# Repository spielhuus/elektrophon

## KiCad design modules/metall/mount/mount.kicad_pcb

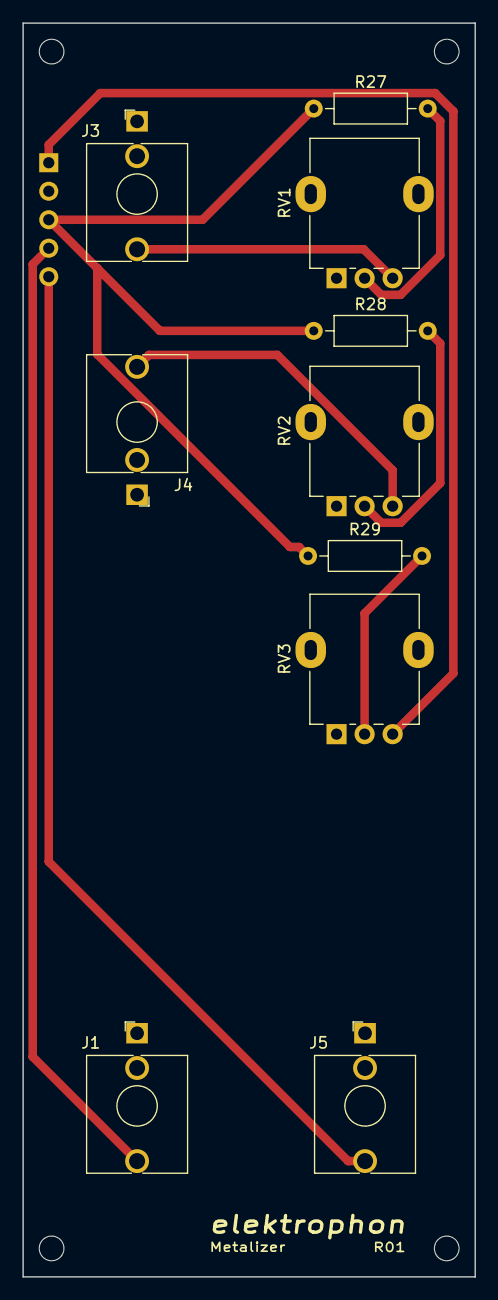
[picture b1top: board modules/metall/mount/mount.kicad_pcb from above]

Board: 2 copper layers, 40.3 x 111.8 mm, 15 parts (1 on the bottom side), 10 nets.

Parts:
H1, H2, H3, H4: MountingHole; MountingHole_2.2mm_M2
J1: INPUT; Jack_3.5mm_WQP-PJ398SM_Vertical
J2: Conn_01x05_Male; PinHeader_1x05_P2.54mm_Vertical
J3: CV1; Jack_3.5mm_WQP-PJ398SM_Vertical
J4: CV2; Jack_3.5mm_WQP-PJ398SM_Vertical
J5: OUT; Jack_3.5mm_WQP-PJ398SM_Vertical
R27, R28, R29: 270k; R_Axial_DIN0207_L6.3mm_D2.5mm_P10.16mm_Horizontal
RV1, RV2, RV3: 100k; Potentiometer_Alpha_RD901F-40-00D_Single_Vertical

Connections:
+15V: J2.1, RV3.3
/CV: J2.3, R27.1, R28.1, R29.1
/IN: J1.T, J2.4
/OUT: J2.5, J5.T
GND: J1.S, J2.2, J3.S, J4.S, J5.S, RV1.1, RV2.1, RV3.1
unnamed: J3.T, RV1.3
unnamed: J4.T, RV2.3
unnamed: R27.2, RV1.2
unnamed: R28.2, RV2.2
unnamed: R29.2, RV3.2

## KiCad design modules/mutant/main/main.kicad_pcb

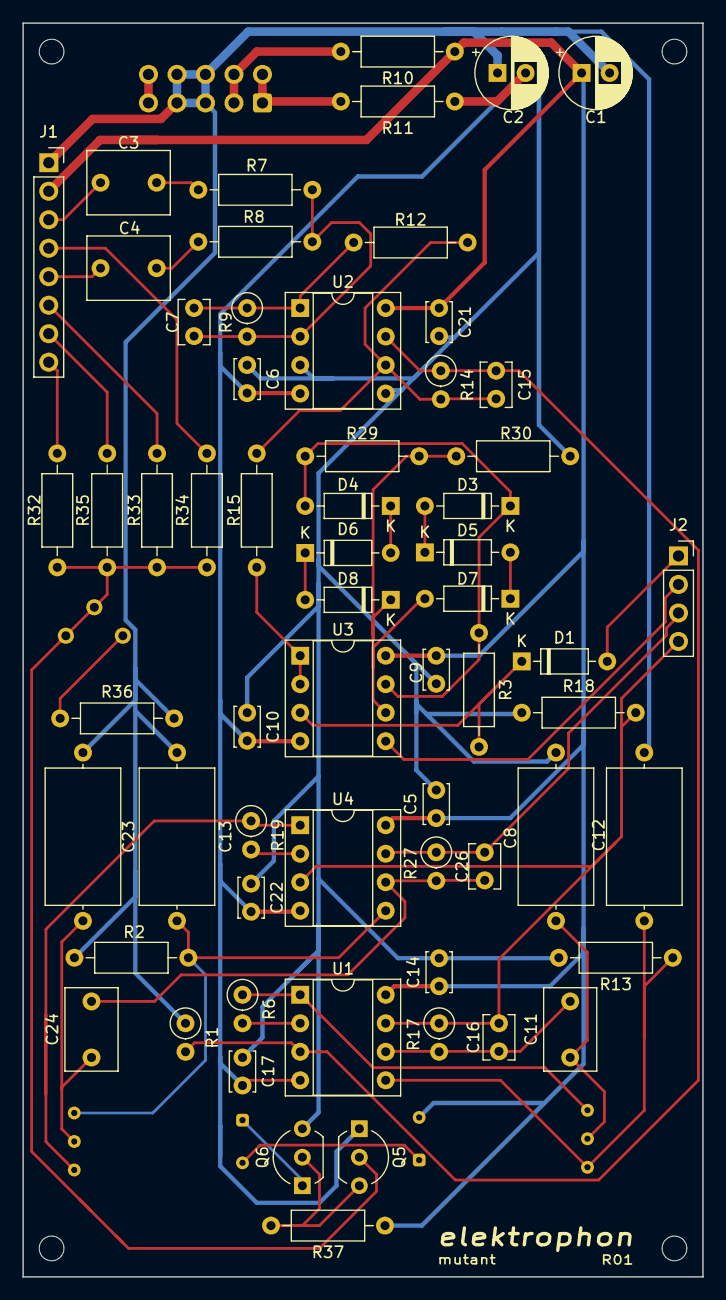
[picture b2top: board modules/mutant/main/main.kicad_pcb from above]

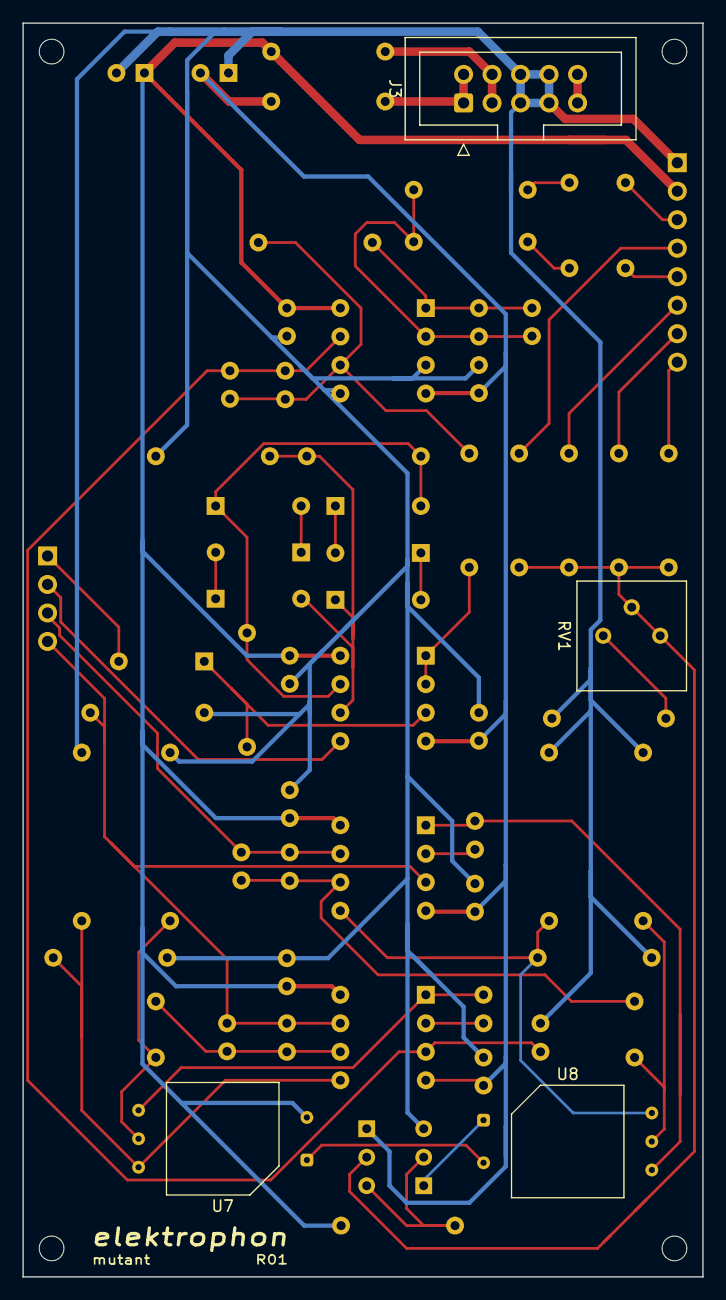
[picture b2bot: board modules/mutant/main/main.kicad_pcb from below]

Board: 2 copper layers, 60.6 x 111.8 mm, 70 parts (4 on the bottom side), 45 nets.

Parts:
C1, C2: 22u; CP_Radial_D6.3mm_P2.50mm
C3, C4: 1u (NP); C_Rect_L7.2mm_W5.5mm_P5.00mm_FKS2_FKP2_MKS2_MKP2
C5, C6, C9, C10, C14, C17, C21, C22: 0.1u; C_Disc_D3.4mm_W2.1mm_P2.50mm
C7, C15, C16, C26: 47p; C_Disc_D3.8mm_W2.6mm_P2.50mm
C8, C23: 220p; C_Axial_L12.0mm_D6.5mm_P15.00mm_Horizontal
C11, C24: 4700p; C_Rect_L7.2mm_W4.5mm_P5.00mm_FKS2_FKP2_MKS2_MKP2
C12, C13: 1000p; C_Axial_L12.0mm_D6.5mm_P15.00mm_Horizontal
D1, D3, D4, D5, D6, D7, D8: 1N4148; D_DO-35_SOD27_P7.62mm_Horizontal
J1: Conn_01x08_Female; PinSocket_1x08_P2.54mm_Vertical
J2: Conn_01x04_Female; PinSocket_1x04_P2.54mm_Vertical
J3: IDC Header; IDC-Header_2x05_P2.54mm_Vertical
Q5: BC557; TO-92_Inline_Wide
Q6: BC547; TO-92_Inline_Wide
R1, R9, R14: 100k; R_Axial_DIN0207_L6.3mm_D2.5mm_P2.54mm_Vertical
R2, R13: 4.7M; R_Axial_DIN0207_L6.3mm_D2.5mm_P10.16mm_Horizontal
R3, R7, R8, R12, R15, R18: 100k; R_Axial_DIN0207_L6.3mm_D2.5mm_P10.16mm_Horizontal
R6, R19: 15k; R_Axial_DIN0207_L6.3mm_D2.5mm_P2.54mm_Vertical
R10, R11: 10; R_Axial_DIN0207_L6.3mm_D2.5mm_P10.16mm_Horizontal
R17, R27: 10k; R_Axial_DIN0207_L6.3mm_D2.5mm_P2.54mm_Vertical
R29: 10k; R_Axial_DIN0207_L6.3mm_D2.5mm_P10.16mm_Horizontal
R30: 1.8k; R_Axial_DIN0207_L6.3mm_D2.5mm_P10.16mm_Horizontal
R32, R33, R34, R35: 110k; R_Axial_DIN0207_L6.3mm_D2.5mm_P10.16mm_Horizontal
R36: 1.5k; R_Axial_DIN0207_L6.3mm_D2.5mm_P10.16mm_Horizontal
R37: 1Meg; R_Axial_DIN0207_L6.3mm_D2.5mm_P10.16mm_Horizontal
REF1, REF2, REF3, REF4: MountingHole_2.2mm_M2
RV1: 1k; Potentiometer_Bourns_3386P_Vertical
U1, U2, U3, U4: TL072; DIP-8_W7.62mm_Socket
U7, U8: VTL5Cx2; PerkinElmer_VTL5Cx2

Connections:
+5V: J3.9, J3.10
+15V: C1.1, C5.1, C9.1, C14.1, C21.1, J1.2, R10.1, R37.1, U1.8, U2.8, U3.8, U4.8, U7.2
-15V: C2.2, C6.2, C10.2, C17.2, C22.2, Q5.1, R11.1, U1.4, U2.4, U3.4, U4.4
/V1a: R6.1, U1.1, U7.5
/V1b: C8.2, C11.1, U7.4
/V1c: C12.2, R13.1, U1.5, U7.3
/V2a: R19.1, U4.1, U8.5
/V2b: C23.2, C24.1, U8.4
/V2c: C13.2, R2.1, U4.5, U8.3
CLIP: D1.2, J2.1
CV: J1.7, R35.2
CV2: J1.8, R32.2
FREQ: J1.4, R34.2
GND: C1.2, C2.1, C5.2, C6.1, C8.1, C9.2, C10.1, C12.1, C13.1, C14.2, C17.1, C21.2, C22.1, C23.1, J1.1, J3.5, J3.6, J3.7, J3.8, Q6.3, R1.1, R2.2, R13.2, R18.1, R30.1, R36.2, U2.3, U2.5
IN_1: C3.2, J1.3
IN_2: C4.2, J1.5
unnamed: C3.1, R7.2
unnamed: C4.1, R8.2
unnamed: C7.1, R9.1, R12.2, U2.1
unnamed: C7.2, R7.1, R8.1, R9.2, U2.2
unnamed: C11.2, C16.2, R17.2, U1.6
unnamed: C15.1, R1.2, R14.1, U1.3, U2.7
unnamed: C15.2, R12.1, R14.2, R15.2, U2.6
unnamed: C24.2, C26.2, R27.2, U4.6
unnamed: D1.1, R3.2, U3.3
unnamed: D3.1, D4.2, R3.1, R29.2, U3.7
unnamed: D3.2, D5.1
unnamed: D4.1, D6.2
unnamed: D5.2, D7.1
unnamed: D6.1, D8.2
unnamed: D7.2, D8.1, R29.1, R30.2, U3.6
unnamed: Q5.2, R32.1, R33.1, R34.1, R35.1, RV1.1, RV1.2
unnamed: Q5.3, Q6.2, R37.2
unnamed: Q6.1, U8.1
unnamed: R6.2, U1.2
unnamed: R15.1, U3.1, U3.2
unnamed: R19.2, U4.2
unnamed: R36.1, RV1.3
unnamed: U7.1, U8.2
OUT_A: C16.1, J2.4, R17.1, R18.2, U1.7, U4.3
OUT_B: C26.1, J2.3, R27.1, U4.7
RES: J2.2, U3.5
VN: J3.1, J3.2, R11.2
VP: J3.3, J3.4, R10.2
V_OCT: J1.6, R33.2

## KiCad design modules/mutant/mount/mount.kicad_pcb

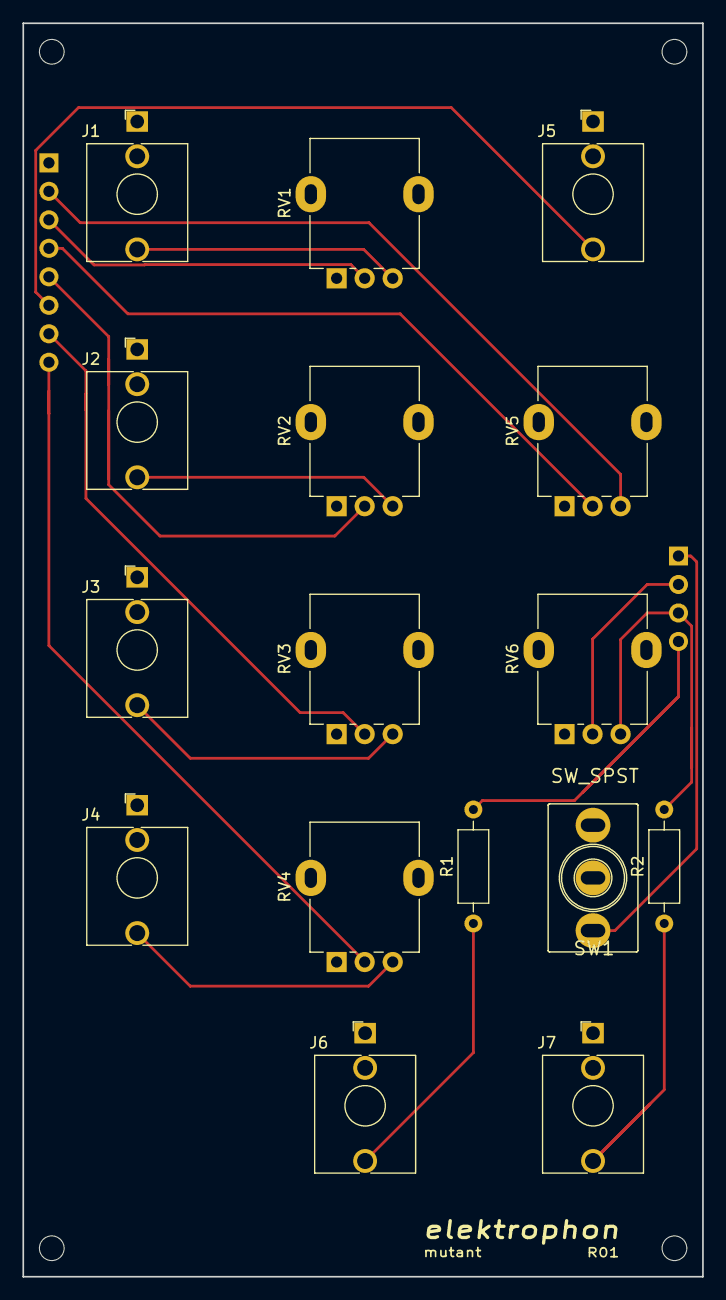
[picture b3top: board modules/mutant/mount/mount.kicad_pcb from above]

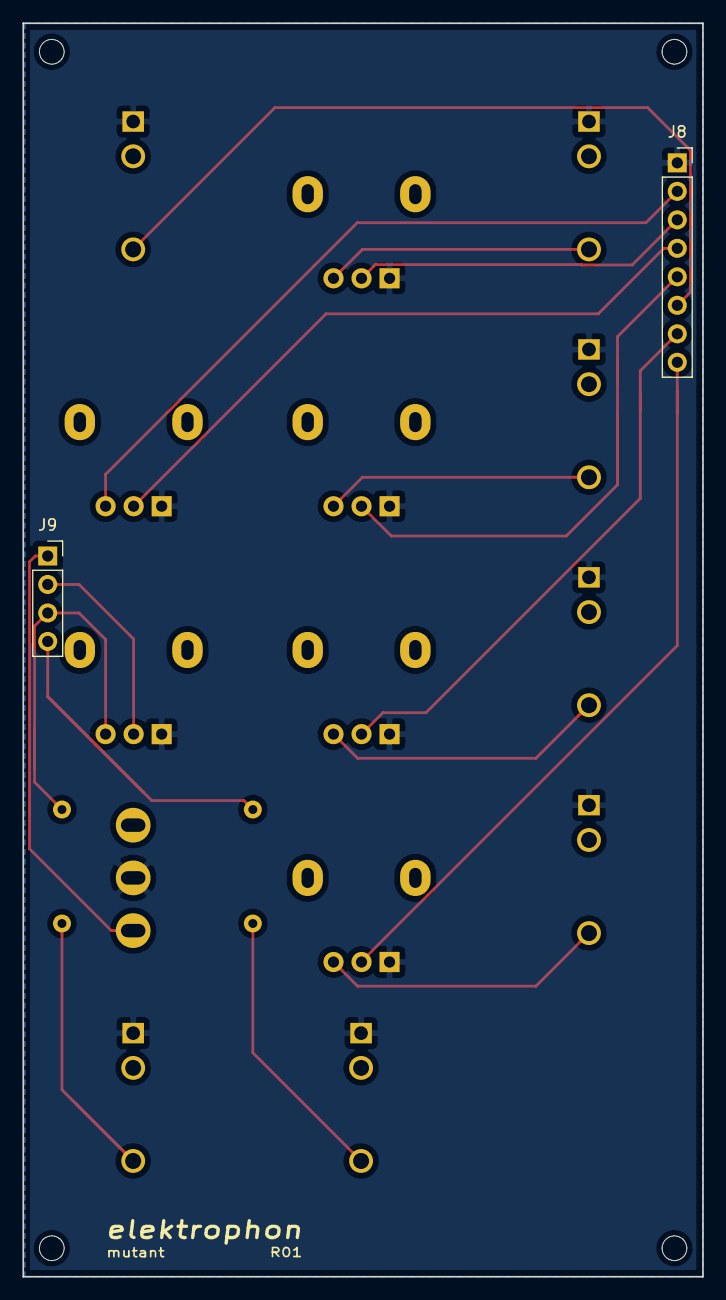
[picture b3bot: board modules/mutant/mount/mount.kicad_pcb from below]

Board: 2 copper layers, 60.6 x 111.8 mm, 22 parts (2 on the bottom side), 18 nets.

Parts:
J1: IN1; Jack_3.5mm_WQP-PJ398SM_Vertical
J2: IN2; Jack_3.5mm_WQP-PJ398SM_Vertical
J3: CV1; Jack_3.5mm_WQP-PJ398SM_Vertical
J4: CV2; Jack_3.5mm_WQP-PJ398SM_Vertical
J5: V/OCT; Jack_3.5mm_WQP-PJ398SM_Vertical
J6: OUt_1; Jack_3.5mm_WQP-PJ398SM_Vertical
J7: OUT_2; Jack_3.5mm_WQP-PJ398SM_Vertical
J8: Conn_01x08_Male; PinSocket_1x08_P2.54mm_Vertical
J9: Conn_01x04_Male; PinSocket_1x04_P2.54mm_Vertical
R1, R2: 1k; R_Axial_DIN0207_L6.3mm_D2.5mm_P10.16mm_Horizontal
REF1, REF2, REF3, REF4: MountingHole_2.2mm_M2
RV1, RV2: 100k; Potentiometer_Alpha_RD901F-40-00D_Single_Vertical
RV3, RV4: 50k; Potentiometer_Alpha_RD901F-40-00D_Single_Vertical
RV5: 20k; Potentiometer_Alpha_RD901F-40-00D_Single_Vertical
RV6: 50k (log); Potentiometer_Alpha_RD901F-40-00D_Single_Vertical
SW1: SW_SPST; SPDT_KIT

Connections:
+15V: J8.2, RV5.3
CLIP: J9.1, SW1.1
CV: J8.7, RV3.2
CV2: J8.8, RV4.2
FREQ: J8.4, RV5.2
GND: J1.S, J2.S, J3.S, J4.S, J5.S, J6.S, J7.S, J8.1, RV1.1, RV2.1, RV3.1, RV4.1, RV5.1, RV6.1, SW1.2
IN_1: J8.3, RV1.2
IN_2: J8.5, RV2.2
unnamed: J1.T, RV1.3
unnamed: J2.T, RV2.3
unnamed: J3.T, RV3.3
unnamed: J4.T, RV4.3
unnamed: J6.T, R1.1
unnamed: J7.T, R2.1
OUT_A: J9.4, R1.2
OUT_B: J9.3, R2.2, RV6.3
RES: J9.2, RV6.2
V_OCT: J5.T, J8.6

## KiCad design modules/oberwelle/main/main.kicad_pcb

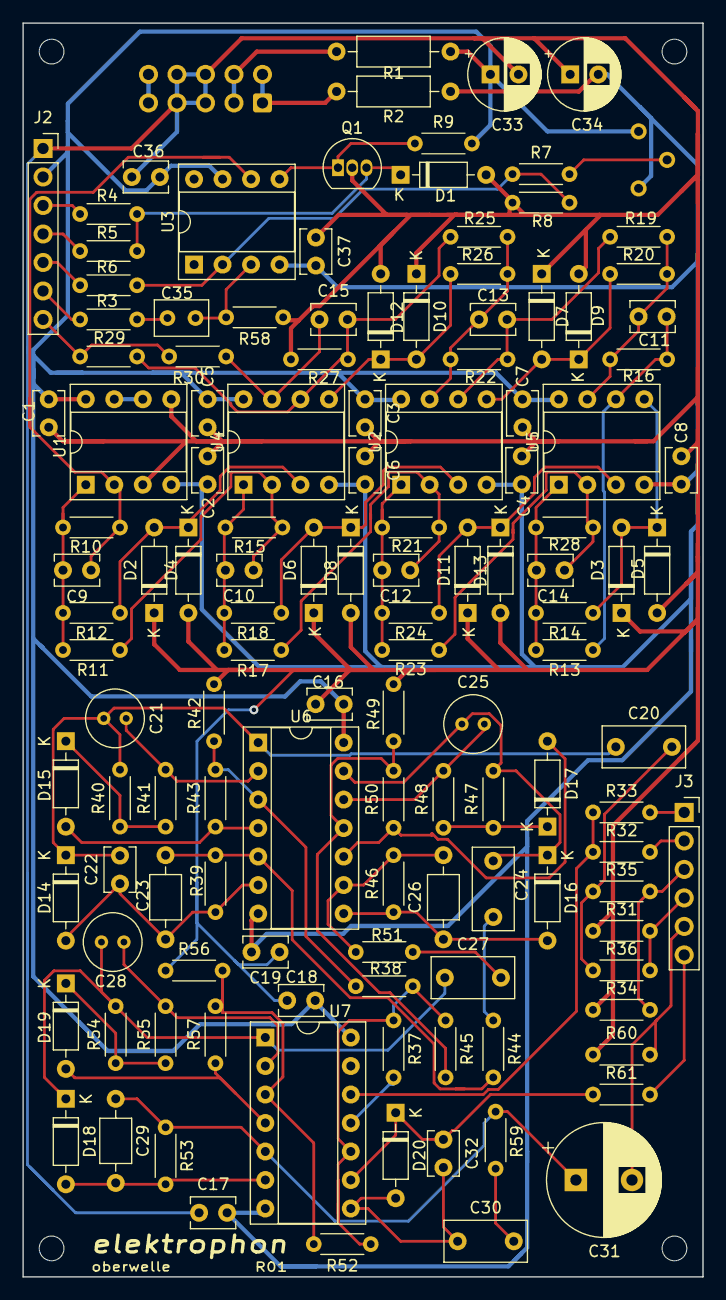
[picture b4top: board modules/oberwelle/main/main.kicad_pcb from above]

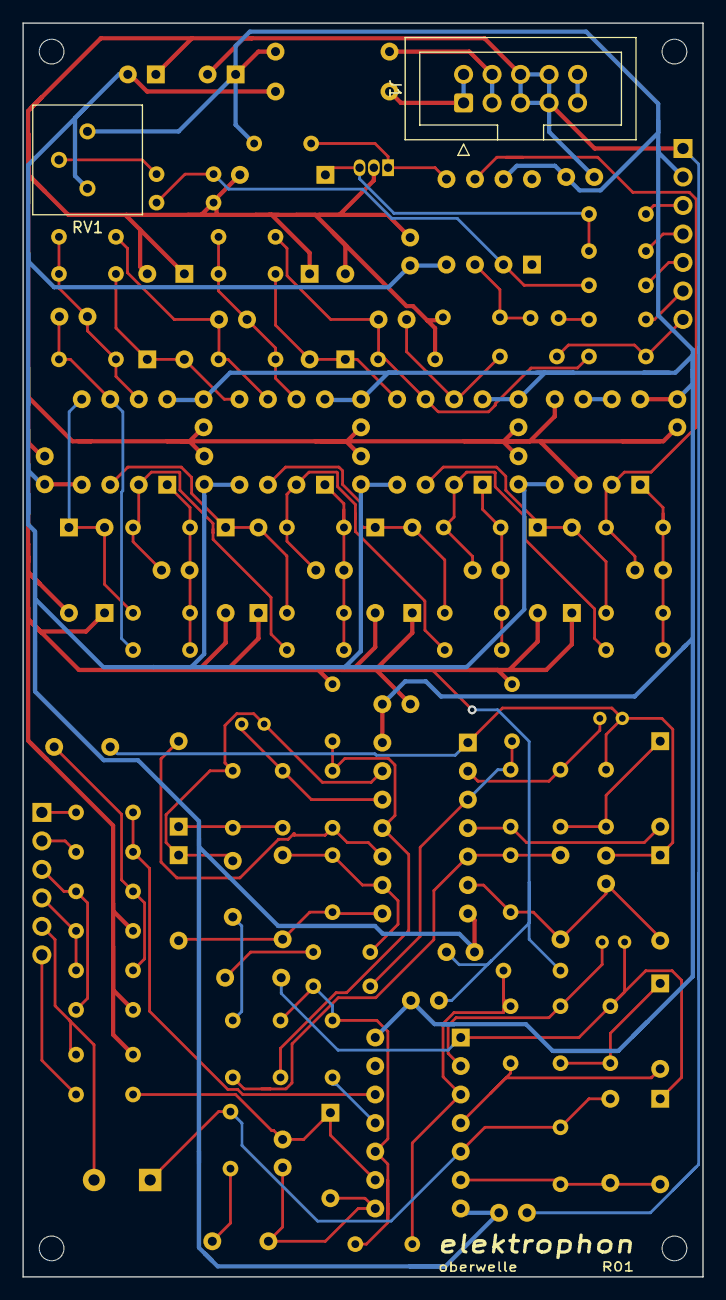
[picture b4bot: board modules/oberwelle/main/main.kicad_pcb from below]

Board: 2 copper layers, 60.6 x 111.8 mm, 134 parts (2 on the bottom side), 74 nets.

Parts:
C1, C2, C3, C4, C5, C6, C7, C8, C16, C17, C18, C19, C36, C37: 0.1u; C_Disc_D3.8mm_W2.6mm_P2.50mm
C9: 150p; C_Disc_D3.8mm_W2.6mm_P2.50mm
C10, C11, C12, C13, C14, C15, C22: 47p; C_Disc_D3.8mm_W2.6mm_P2.50mm
C20, C24, C27, C30: 47n; C_Rect_L7.2mm_W3.5mm_P5.00mm_FKS2_FKP2_MKS2_MKP2
C21: 1u (BP); C_Radial_D5.0mm_H7.0mm_P2.00mm
C23, C26, C29: 30p; C_Axial_L3.8mm_D2.6mm_P7.50mm_Horizontal
C25, C28: 1u (BP); C_Radial_D5.0mm_H5.0mm_P2.00mm
C31: 47u; CP_Radial_D10.0mm_P5.00mm
C32: 30p; C_Disc_D3.8mm_W2.6mm_P2.50mm
C33, C34: 22u; CP_Radial_D6.3mm_P2.50mm
C35: 220n; C_Rect_L4.6mm_W3.0mm_P2.50mm_MKS02_FKP02
D1, D2, D3, D4, D5, D6, D7, D8, D9, D10, D11, D12, D13, D14, D15, D16, D17, D18, D19: 1N4148; D_DO-35_SOD27_P7.62mm_Horizontal
D20: 4.3V/400mW; D_DO-35_SOD27_P7.62mm_Horizontal
J1: IDC Header; IDC-Header_2x05_P2.54mm_Vertical
J2: Conn_01x07_Female; PinSocket_1x07_P2.54mm_Vertical
J3: Conn_01x06_Female; PinSocket_1x06_P2.54mm_Vertical
Q1: BC557; TO-92_Inline
R1, R2: 10; R_Axial_DIN0207_L6.3mm_D2.5mm_P10.16mm_Horizontal
R3, R6, R11, R13, R15, R16, R17, R19, R21, R22, R23, R25, R28, R29, R31, R33, R34, R59, R60: 100k; R_Axial_DIN0204_L3.6mm_D1.6mm_P5.08mm_Horizontal
R4: 47k; R_Axial_DIN0204_L3.6mm_D1.6mm_P5.08mm_Horizontal
R5: 15k; R_Axial_DIN0204_L3.6mm_D1.6mm_P5.08mm_Horizontal
R7: 3.3meg; R_Axial_DIN0204_L3.6mm_D1.6mm_P5.08mm_Horizontal
R8, R58: 1.5k; R_Axial_DIN0204_L3.6mm_D1.6mm_P5.08mm_Horizontal
R9: 6.8meg; R_Axial_DIN0204_L3.6mm_D1.6mm_P5.08mm_Horizontal
R10: 82k; R_Axial_DIN0204_L3.6mm_D1.6mm_P5.08mm_Horizontal
R12, R14, R18, R20, R24, R26: 33k; R_Axial_DIN0204_L3.6mm_D1.6mm_P5.08mm_Horizontal
R27: 10k; R_Axial_DIN0204_L3.6mm_D1.6mm_P5.08mm_Horizontal
R30: 330; R_Axial_DIN0204_L3.6mm_D1.6mm_P5.08mm_Horizontal
R32, R38: 220k; R_Axial_DIN0204_L3.6mm_D1.6mm_P5.08mm_Horizontal
R35, R36, R43, R44, R51: 1meg; R_Axial_DIN0204_L3.6mm_D1.6mm_P5.08mm_Horizontal
R37: 150k; R_Axial_DIN0204_L3.6mm_D1.6mm_P5.08mm_Horizontal
R39, R46, R53, R57: 2.2meg; R_Axial_DIN0204_L3.6mm_D1.6mm_P5.08mm_Horizontal
R40, R41, R47, R48, R54, R55: 10meg; R_Axial_DIN0204_L3.6mm_D1.6mm_P5.08mm_Horizontal
R42, R49, R56: 820k; R_Axial_DIN0204_L3.6mm_D1.6mm_P5.08mm_Horizontal
R45: 330k; R_Axial_DIN0204_L3.6mm_D1.6mm_P5.08mm_Horizontal
R50: 1.5meg; R_Axial_DIN0204_L3.6mm_D1.6mm_P5.08mm_Horizontal
R52: 470k; R_Axial_DIN0204_L3.6mm_D1.6mm_P5.08mm_Horizontal
R61: 3.3k; R_Axial_DIN0204_L3.6mm_D1.6mm_P5.08mm_Horizontal
REF1, REF2, REF3, REF4: MountingHole_2.2mm_M2
RV1: 100k; Potentiometer_Bourns_3386P_Vertical
U1, U2, U4, U5: TL072; DIP-8_W7.62mm_Socket
U3: CA3080; DIP-8_W7.62mm_Socket
U6, U7: LM3900; DIP-14_W7.62mm_Socket

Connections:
+5V: J1.9, J1.10
+15V: C1.1, C3.1, C5.1, C7.1, C16.1, C18.1, C33.1, C36.1, J2.2, R1.1, R9.2, RV1.1, U1.8, U2.8, U3.7, U4.8, U5.8, U6.14, U7.14
-15V: C2.2, C4.2, C6.2, C8.2, C17.2, C19.2, C34.2, C37.2, R2.1, RV1.3, U1.4, U2.4, U3.4, U4.4, U5.4, U6.7, U7.7
CV: J3.1, R33.2
CV_INITIAL: J3.2, R32.2
GND: C1.2, C2.1, C3.2, C4.1, C5.2, C6.1, C7.2, C8.1, C16.2, C17.1, C18.2, C19.1, C33.2, C34.1, C36.2, C37.1, D1.2, D2.1, D3.1, D4.2, D5.2, D6.1, D7.1, D8.2, D9.2, D10.1, D11.1, D12.2, D13.2, J1.5, J1.6, J1.7, J1.8, J2.1, Q1.2, R8.1, R27.1, R31.1, R34.1, R42.1, R49.1, R56.1, R58.1, R60.1, U1.3, U1.5
IN_1: J3.3, R34.2, R35.2
IN_2: J3.4, R31.2, R36.2
M_CV: J2.4, R5.2
M_CV_INITIAL: J2.3, R4.2
M_IN_1: J2.6, R3.2
M_IN_2: J2.5, R6.2
M_OUT: J2.7, R29.1, R30.1
unnamed: C9.1, R10.1, R11.2, R12.2, U1.1
unnamed: C9.2, R10.2, U1.2, U3.6
unnamed: C10.1, R15.1, R17.2, R18.2, U4.1
unnamed: C10.2, R11.1, R15.2, U4.2
unnamed: C11.1, R16.1, R19.2, R20.2, U5.7
unnamed: C11.2, R13.1, R16.2, U5.6
unnamed: C12.1, R21.1, R23.2, R24.2, U2.1
unnamed: C12.2, R17.1, R21.2, U2.2
unnamed: C13.1, R22.1, R25.2, R26.2, U2.7
unnamed: C13.2, R19.1, R22.2, U2.6
unnamed: C14.1, R13.2, R14.2, R28.1, U5.1
unnamed: C14.2, R23.1, R28.2, U5.2
unnamed: C15.1, R30.2, U4.7
unnamed: C15.2, R25.1, R27.2, R29.2, U4.6
unnamed: C20.1, C21.1, C22.2, D14.1, R40.2, U6.1
unnamed: C20.2, R35.1, R36.1
unnamed: C21.2, R41.2, U6.2
unnamed: C22.1, C23.2, D14.2, R39.2, U6.6
unnamed: C23.1, R39.1, R44.2, U6.5
unnamed: C24.1, C25.1, D16.1, R47.2, U6.13
unnamed: C24.2, R44.1
unnamed: C25.2, R48.2, U6.12
unnamed: C26.1, R46.1, R51.2, U6.9
unnamed: C26.2, D16.2, R46.2, U6.8
unnamed: C27.1, C28.1, D18.1, R54.2, U7.1
unnamed: C27.2, R51.1
unnamed: C28.2, R55.2, U7.2
unnamed: C29.1, C31.1, R53.1, R59.2, U7.5
unnamed: C29.2, D18.2, R53.2, U7.6
unnamed: C30.1, C32.2, D20.2, U7.8
unnamed: C30.2, R59.1
unnamed: C32.1, D20.1, R61.1, U7.9
unnamed: C35.1, R58.2, U3.3
unnamed: C35.2, R3.1
unnamed: D1.1, Q1.3, R4.1, R5.1
unnamed: D2.2, D4.1, R12.1, U4.3
unnamed: D3.2, D5.1, R14.1, U5.5
unnamed: D6.2, D8.1, R18.1, U2.3
unnamed: D7.2, D9.1, R20.1, U2.5
unnamed: D10.2, D12.1, R26.1, U4.5
unnamed: D11.2, D13.1, R24.1, U5.3
unnamed: D15.1, R40.1, R41.1
unnamed: D15.2, R43.1, U6.4
unnamed: D17.1, R47.1, R48.1
unnamed: D17.2, R50.1, U6.10
unnamed: D19.1, R54.1, R55.1
unnamed: D19.2, R57.1, U7.4
unnamed: Q1.1, R9.1, U3.5
unnamed: R6.1, R7.1, R8.2, U3.2
unnamed: R7.2, RV1.2
unnamed: R32.1, R33.1, U7.12
unnamed: R37.1, R38.1, R45.1, R52.1, U7.10
unnamed: R37.2, U7.11
unnamed: R38.2, R42.2, R43.2, U6.3
unnamed: R45.2, R49.2, R50.2, U6.11
unnamed: R52.2, R56.2, R57.2, U7.3
unnamed: U1.6, U1.7
OUT_1: C31.2, J3.5, R60.2
OUT_2: J3.6, R61.2
VN: J1.1, J1.2, R2.2
VP: J1.3, J1.4, R1.2

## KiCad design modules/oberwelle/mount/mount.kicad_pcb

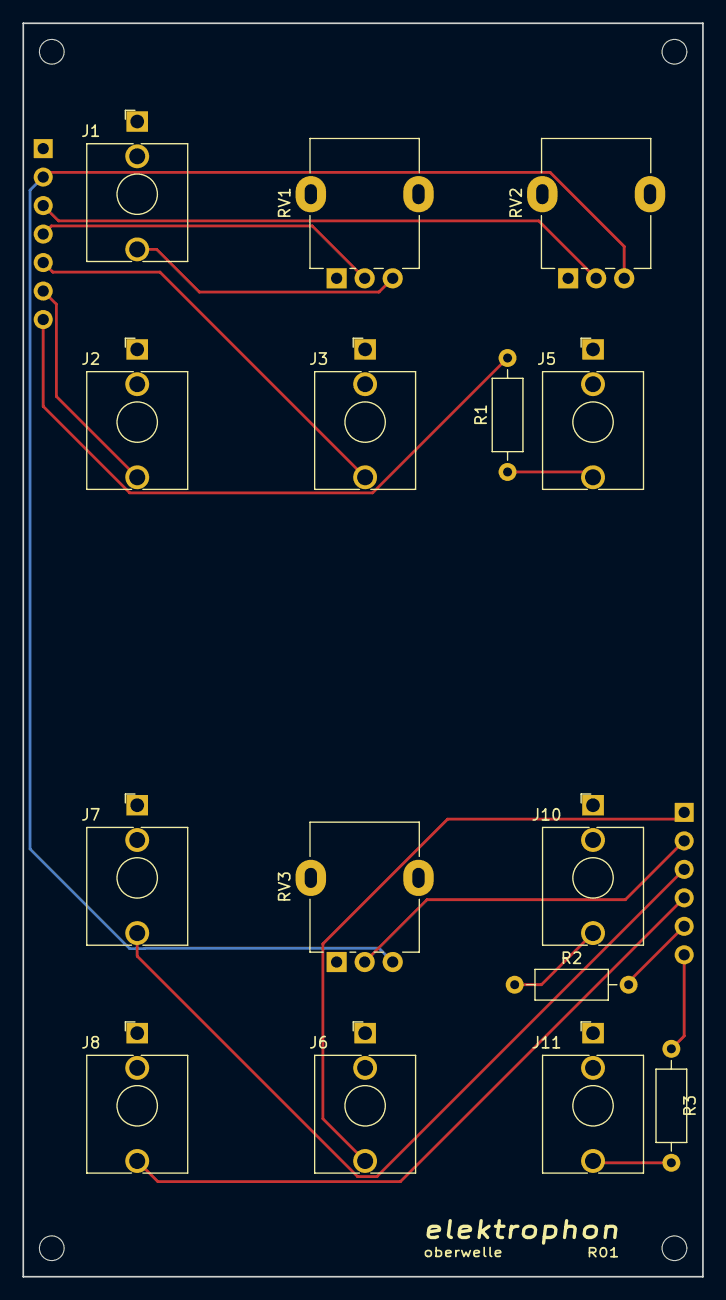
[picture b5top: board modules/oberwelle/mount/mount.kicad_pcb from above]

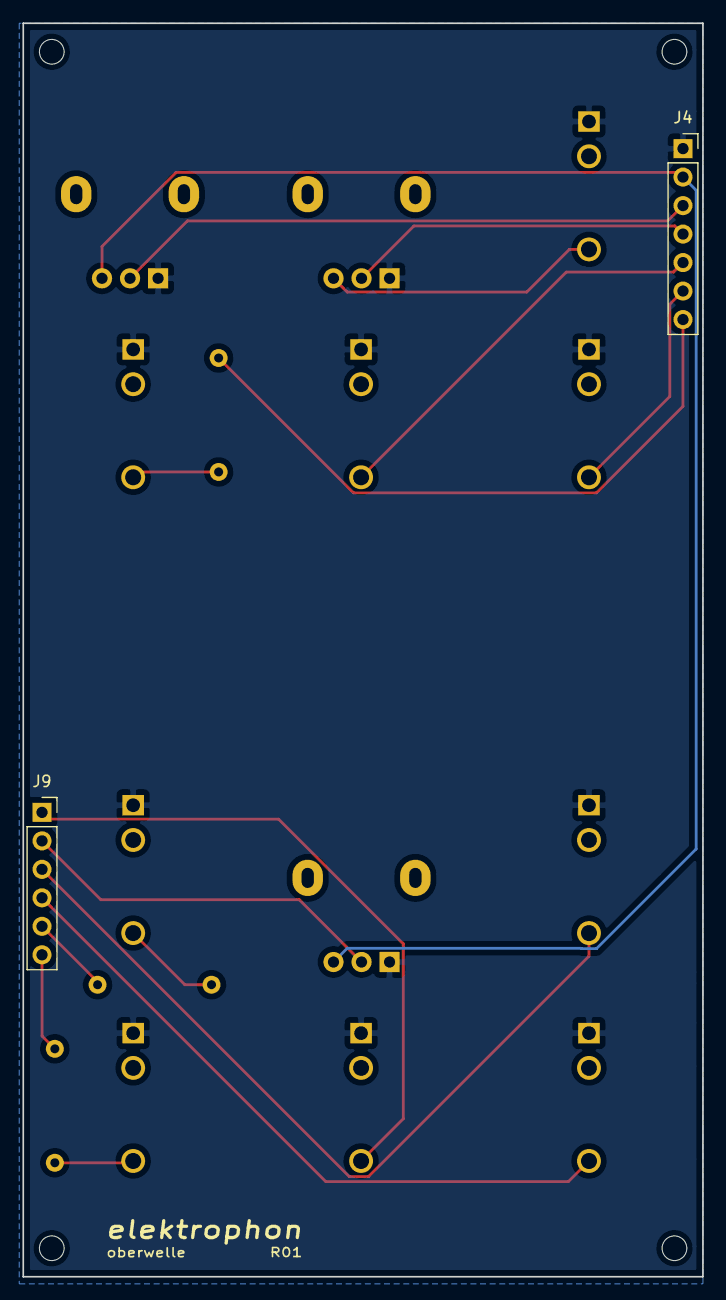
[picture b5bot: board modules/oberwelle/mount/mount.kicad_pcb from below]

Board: 2 copper layers, 60.6 x 111.8 mm, 22 parts (2 on the bottom side), 17 nets.

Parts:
J1: CV2; Jack_3.5mm_WQP-PJ398SM_Vertical
J2, J3, J6, J7, J8: V/OCT; Jack_3.5mm_WQP-PJ398SM_Vertical
J4: Conn_01x07_Male; PinSocket_1x07_P2.54mm_Vertical
J5, J10, J11: OUt_1; Jack_3.5mm_WQP-PJ398SM_Vertical
J9: Conn_01x06_Male; PinSocket_1x06_P2.54mm_Vertical
R1, R2, R3: 1k; R_Axial_DIN0207_L6.3mm_D2.5mm_P10.16mm_Horizontal
REF1, REF2, REF3, REF4: MountingHole_2.2mm_M2
REF5: elektrophon logo
RV1, RV2, RV3: 50k; Potentiometer_Alpha_RD901F-40-00D_Single_Vertical

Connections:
+15V: J4.2, RV2.3, RV3.3
CV: J6.T, J9.1
CV_INITIAL: J9.2, RV3.2
GND: J1.S, J2.S, J3.S, J4.1, J5.S, J6.S, J7.S, J8.S, J10.S, J11.S, RV1.1, RV2.1, RV3.1
IN_1: J7.T, J9.3
IN_2: J8.T, J9.4
M_CV: J4.4, RV1.2
M_CV_INITIAL: J4.3, RV2.2
M_IN_1: J2.T, J4.6
M_IN_2: J3.T, J4.5
M_OUT: J4.7, R1.2
unnamed: J1.T, RV1.3
unnamed: J5.T, R1.1
unnamed: J10.T, R2.1
unnamed: J11.T, R3.1
OUT_1: J9.5, R2.2
OUT_2: J9.6, R3.2

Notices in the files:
modules/metall/mount/mount.kicad_pcb:
License CC BY 4.0 - Attribution 4.0 International
